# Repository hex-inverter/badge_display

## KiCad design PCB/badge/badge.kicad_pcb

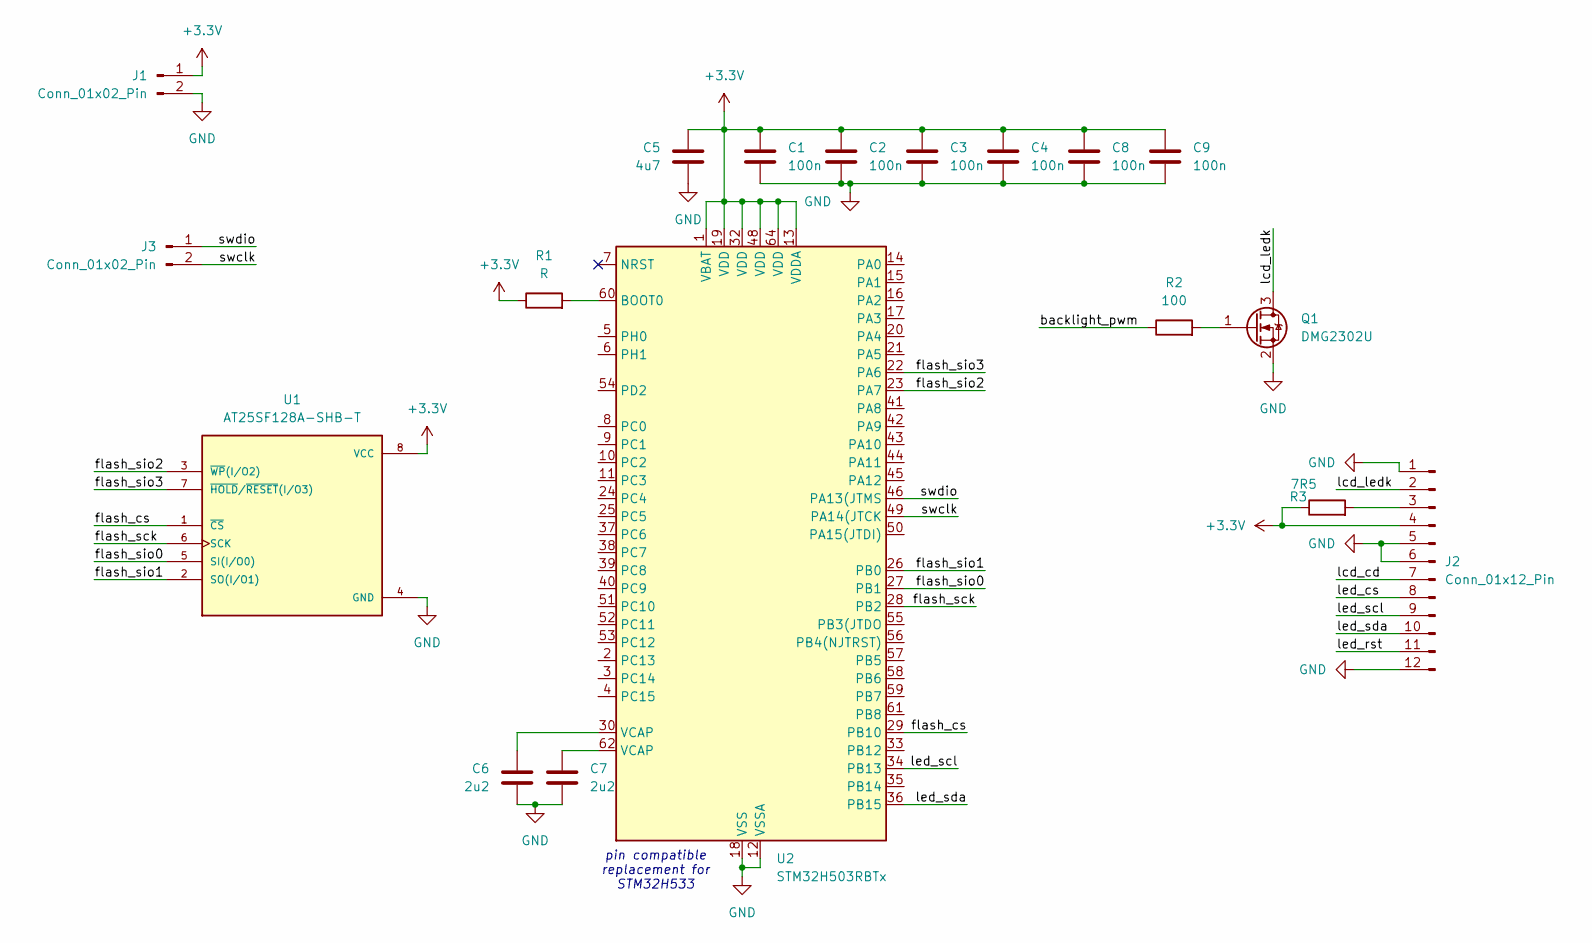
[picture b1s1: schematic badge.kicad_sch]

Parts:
C1, C2, C3, C4, C8, C9: 100n; C_0603_1608Metric_Pad1.08x0.95mm_HandSolder
C5: 4u7; C_0603_1608Metric_Pad1.08x0.95mm_HandSolder
C6, C7: 2u2; C_0603_1608Metric_Pad1.08x0.95mm_HandSolder
J1, J3: Conn_01x02_Pin; 2_pads
J2: Conn_01x12_Pin; LH128R
Q1: DMG2302U; SOT-23
R1: R; R_0603_1608Metric_Pad0.98x0.95mm_HandSolder
R2: 100; R_0603_1608Metric_Pad0.98x0.95mm_HandSolder
R3: 7R5; R_0603_1608Metric_Pad0.98x0.95mm_HandSolder
U1: AT25SF128A-SHB-T; SOIC-8W_5.3x5.3mm_P1.27mm; PARTREV F
U2: STM32H503RBTx; LQFP-64_10x10mm_P0.5mm

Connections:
+3.3V: C1.1, C2.1, C3.1, C4.1, C5.1, C8.1, C9.1, J1.1, J2.4, R1.1, R3.1, U1.8 (VCC), U2.1 (VBAT), U2.13 (VDDA), U2.19 (VDD), U2.32 (VDD), U2.48 (VDD), U2.64 (VDD)
/backlight_pwm: R2.1
/flash_cs: U1.1 (~CS), U2.29 (PB10)
/flash_sck: U1.6 (SCK), U2.28 (PB2)
/flash_sio0: U1.5 (SI(I/O0)), U2.27 (PB1)
/flash_sio1: U1.2 (SO(I/O1)), U2.26 (PB0)
/flash_sio2: U1.3 (~WP(I/O2)), U2.23 (PA7)
/flash_sio3: U1.7 (~HOLD/~RESET(I/O3)), U2.22 (PA6)
/lcd_cd: J2.7
/lcd_ledk: J2.2, Q1.3 (D)
/led_cs: J2.8
/led_rst: J2.11
/led_scl: J2.9, U2.34 (PB13)
/led_sda: J2.10, U2.36 (PB15)
/swclk: J3.2, U2.49 (PA14(JTCK)
/swdio: J3.1, U2.46 (PA13(JTMS)
GND: C1.2, C2.2, C3.2, C4.2, C5.2, C6.2, C7.2, C8.2, C9.2, J1.2, J2.1, J2.5, J2.6, J2.12, Q1.2 (S), U1.4 (GND), U2.12 (VSSA), U2.18 (VSS), U2.31 (VSS), U2.47 (VSS), U2.63 (VSS)
unnamed: C6.1, U2.30 (VCAP)
unnamed: C7.1, U2.62 (VCAP)
unnamed: J2.3, R3.2
unnamed: Q1.1 (G), R2.2
unnamed: R1.2, U2.60 (BOOT0)

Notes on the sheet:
pin compatible replacement for STM32H533

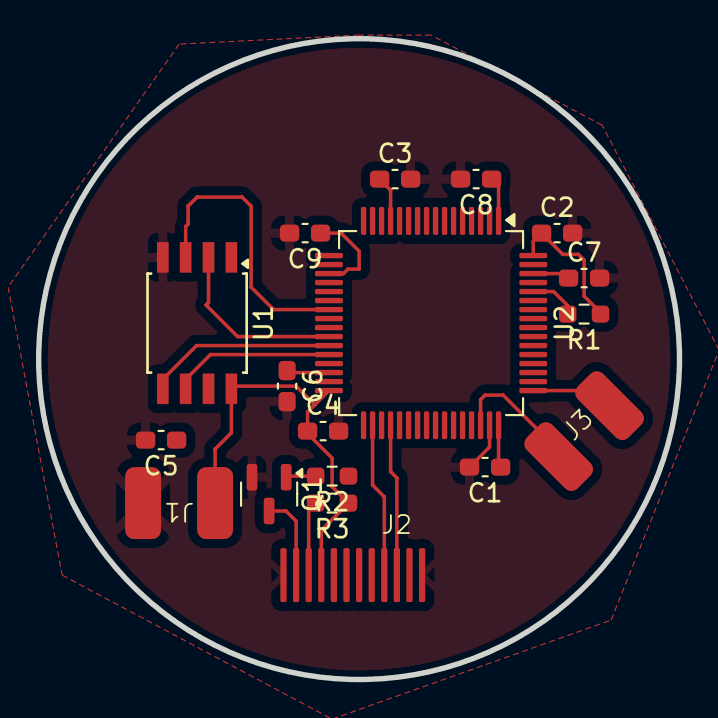
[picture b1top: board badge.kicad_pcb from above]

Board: 2 copper layers, 35.6 x 35.6 mm, 18 parts (0 on the bottom side), 18 nets.

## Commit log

2024-10-14 working drivers for LH128R display
2024-10-16 GIF parser - unfinished solution with linked list. Trying faster solution with arrays next.
2026-05-16 pcb updates
